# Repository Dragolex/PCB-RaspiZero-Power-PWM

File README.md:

# PCB-RaspiZero-Power-PWM
My first mostly successful try at a printed circuit board. It hosts a PCA9685 16xPWM generator and mosfets for every channel.
Controled via I2C from a Raspberry PI or an Adruino it can be used to dim loads of 7A and more. 
The board's shape, pins and hole palcement equals a Raspberry Pi Zero and therefore allows to mount it directly ontop and still use all pins.  
The Mosfets are N channel mosfets meaning only the Ground is common for all of them and on the PCB. Therefore loads of different voltages can be used simultaneously.

**The project can be opened with Eagle 9.1.1 or newer (importing into odler versions should be possible too).**

Boards based on Gerber files exported from this project have been produced by https://jlcpcb.com/
Samples have been soldered by myself and tested successfully with a bunch of different loads. Unfortunately it turned out that the diodes on the backside of the PCB are efectively useless because not sensefully placed in the scheme. Therefore inductive loads like motors still require separate flyback diodes!

Photos of a project using this comes soon.

## Credits
The PCA9685 and Raspberry scheme footprints are from Adafruit:
https://learn.adafruit.com/16-channel-pwm-servo-driver/downloads

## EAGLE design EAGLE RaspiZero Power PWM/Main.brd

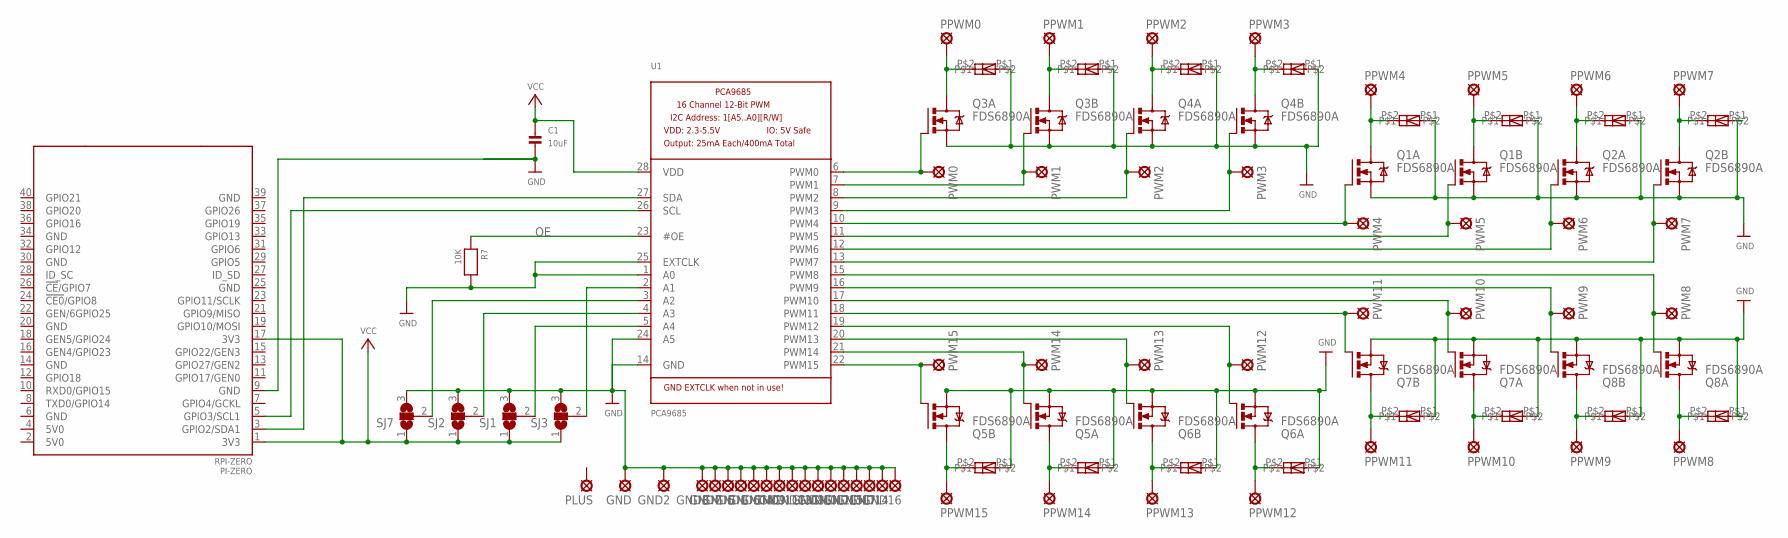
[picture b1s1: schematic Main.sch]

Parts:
C1: 10uF; 0805
GND, GND1, GND2, GND3, GND4, GND5, GND6, GND7, GND8, GND9, GND10, GND11, GND12, GND13, GND14, GND15, GND16, GND17: LSP11
PI-ZERO: RPI-ZERO; RASPBERRYPI_BASTELSTUBE_V13_RASPI_BOARD_B+_FULL
PLUS: LSP11
PPWM0, PPWM1, PPWM2, PPWM3, PPWM4, PPWM5, PPWM6, PPWM7, PPWM8, PPWM9, PPWM10, PPWM11, PPWM12, PPWM13, PPWM14, PPWM15: LSP11
PWM0, PWM1, PWM2, PWM3, PWM4, PWM5, PWM6, PWM7, PWM8, PWM9, PWM10, PWM11, PWM12, PWM13, PWM14, PWM15: LSP11
Q1, Q2, Q3, Q4, Q5, Q6, Q7, Q8: FDS6890A; M08A
R7: 10K; 0805
SJ1, SJ2, SJ3, SJ7: SJ2W; SJ_2
U1: PCA9685; MICROBUILDER_TSSOP28
U$6, U$7, U$8, U$9, U$10, U$11, U$12, U$13, U$14, U$15, U$16, U$17, U$18, U$19, U$20, U$21: OPTIONALDIODE

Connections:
GND: C1.2, GND.MP, GND1.MP, GND2.MP, GND3.MP, GND4.MP, GND5.MP, GND6.MP, GND7.MP, GND8.MP, GND9.MP, GND10.MP, GND11.MP, GND12.MP, GND13.MP, GND14.MP, GND15.MP, GND16.MP, GND17.MP, PI-ZERO.9 (GND), Q1.1 (S), Q1.3 (S), Q2.1 (S), Q2.3 (S), Q3.1 (S), Q3.3 (S), Q4.1 (S), Q4.3 (S), Q5.1 (S), Q5.3 (S), Q6.1 (S), Q6.3 (S), Q7.1 (S), Q7.3 (S), Q8.1 (S), Q8.3 (S), R7.2, SJ1.3, SJ2.3, SJ3.3, SJ7.3, U1.1 (A0), U1.14 (GND), U1.24 (A5), U1.25 (EXTCLK), U$6.P$1, U$7.P$1, U$8.P$1, U$9.P$1, U$10.P$1, U$11.P$1, U$12.P$1, U$13.P$1, U$14.P$1, U$15.P$1, U$16.P$1, U$17.P$1, U$18.P$1, U$19.P$1, U$20.P$1, U$21.P$1
LPWM0: PWM0.MP, Q3.2 (G), U1.6 (PWM0)
LPWM1: PWM1.MP, Q3.4 (G), U1.7 (PWM1)
LPWM2: PWM2.MP, Q4.2 (G), U1.8 (PWM2)
LPWM3: PWM3.MP, Q4.4 (G), U1.9 (PWM3)
LPWM4: PWM4.MP, Q1.2 (G), U1.10 (PWM4)
LPWM5: PWM5.MP, Q1.4 (G), U1.11 (PWM5)
LPWM6: PWM6.MP, Q2.2 (G), U1.12 (PWM6)
LPWM7: PWM7.MP, Q2.4 (G), U1.13 (PWM7)
LPWM8: PWM8.MP, Q8.2 (G), U1.15 (PWM8)
LPWM9: PWM9.MP, Q8.4 (G), U1.16 (PWM9)
LPWM10: PWM10.MP, Q7.2 (G), U1.17 (PWM10)
LPWM11: PWM11.MP, Q7.4 (G), U1.18 (PWM11)
LPWM12: PWM12.MP, Q6.2 (G), U1.19 (PWM12)
LPWM13: PWM13.MP, Q6.4 (G), U1.20 (PWM13)
LPWM14: PWM14.MP, Q5.2 (G), U1.21 (PWM14)
LPWM15: PWM15.MP, Q5.4 (G), U1.22 (PWM15)
unnamed: PPWM0.MP, Q3.7 (D), Q3.8 (D), U$7.P$2
unnamed: PPWM1.MP, Q3.5 (D), Q3.6 (D), U$8.P$2
unnamed: PPWM2.MP, Q4.7 (D), Q4.8 (D), U$9.P$2
unnamed: PPWM3.MP, Q4.5 (D), Q4.6 (D), U$10.P$2
unnamed: PPWM4.MP, Q1.7 (D), Q1.8 (D), U$11.P$2
unnamed: PPWM5.MP, Q1.5 (D), Q1.6 (D), U$12.P$2
unnamed: PPWM6.MP, Q2.7 (D), Q2.8 (D), U$13.P$2
unnamed: PPWM7.MP, Q2.5 (D), Q2.6 (D), U$14.P$2
unnamed: PPWM15.MP, Q5.5 (D), Q5.6 (D), U$6.P$2
unnamed: PPWM14.MP, Q5.7 (D), Q5.8 (D), U$21.P$2
unnamed: PPWM13.MP, Q6.5 (D), Q6.6 (D), U$20.P$2
unnamed: PPWM12.MP, Q6.7 (D), Q6.8 (D), U$19.P$2
unnamed: PPWM11.MP, Q7.5 (D), Q7.6 (D), U$18.P$2
unnamed: PPWM10.MP, Q7.7 (D), Q7.8 (D), U$17.P$2
unnamed: PPWM9.MP, Q8.5 (D), Q8.6 (D), U$16.P$2
unnamed: PPWM8.MP, Q8.7 (D), Q8.8 (D), U$15.P$2
unnamed: PI-ZERO.5 (GPIO3/SCL1), U1.26 (SCL)
unnamed: SJ7.2, U1.3 (A2)
unnamed: SJ2.2, U1.4 (A3)
unnamed: SJ1.2, U1.5 (A4)
unnamed: PI-ZERO.3 (GPIO2/SDA1), U1.27 (SDA)
unnamed: SJ3.2, U1.2 (A1)
OE: R7.1, U1.23 (#OE)
VCC: C1.1, PI-ZERO.1 (3V3), PI-ZERO.17 (3V3), SJ1.1, SJ2.1, SJ3.1, SJ7.1, U1.28 (VDD)

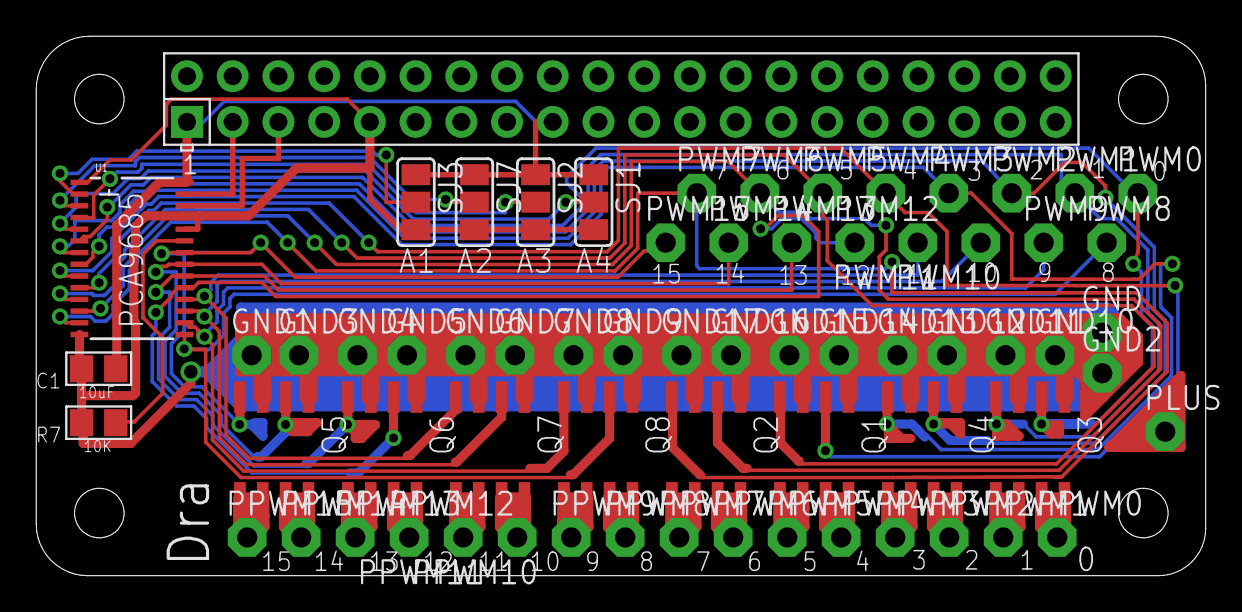
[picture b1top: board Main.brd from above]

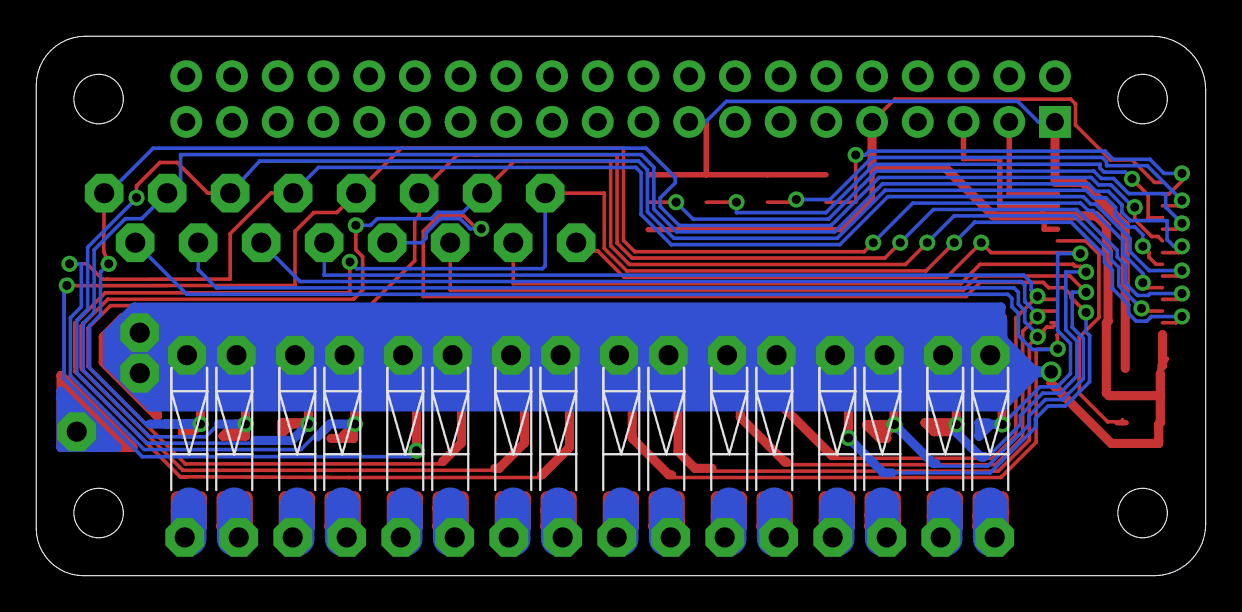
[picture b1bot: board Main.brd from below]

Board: 2 copper layers, 65.0 x 30.0 mm, 83 parts (16 on the bottom side), 41 nets.

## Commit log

2019-03-30 Eagle Files
2019-03-30 Gerber files
2019-03-30 Full Readme
2019-03-30 Added Images
2019-03-30 Added images and credits
2019-03-30 No language to detect
